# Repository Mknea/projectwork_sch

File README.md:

# Project work pcb design

This repository contains the KiCAD schematic and pcb layout files used in Project work course. The designed boards were used in conjunction with developed mobile app to automate a popular finnish outdoor game, Mölkky.

Both macro- and microboard-versions of the design were manufactured, components were soldered in, and the proper functioning of the whole product was both verified and demonstrated.

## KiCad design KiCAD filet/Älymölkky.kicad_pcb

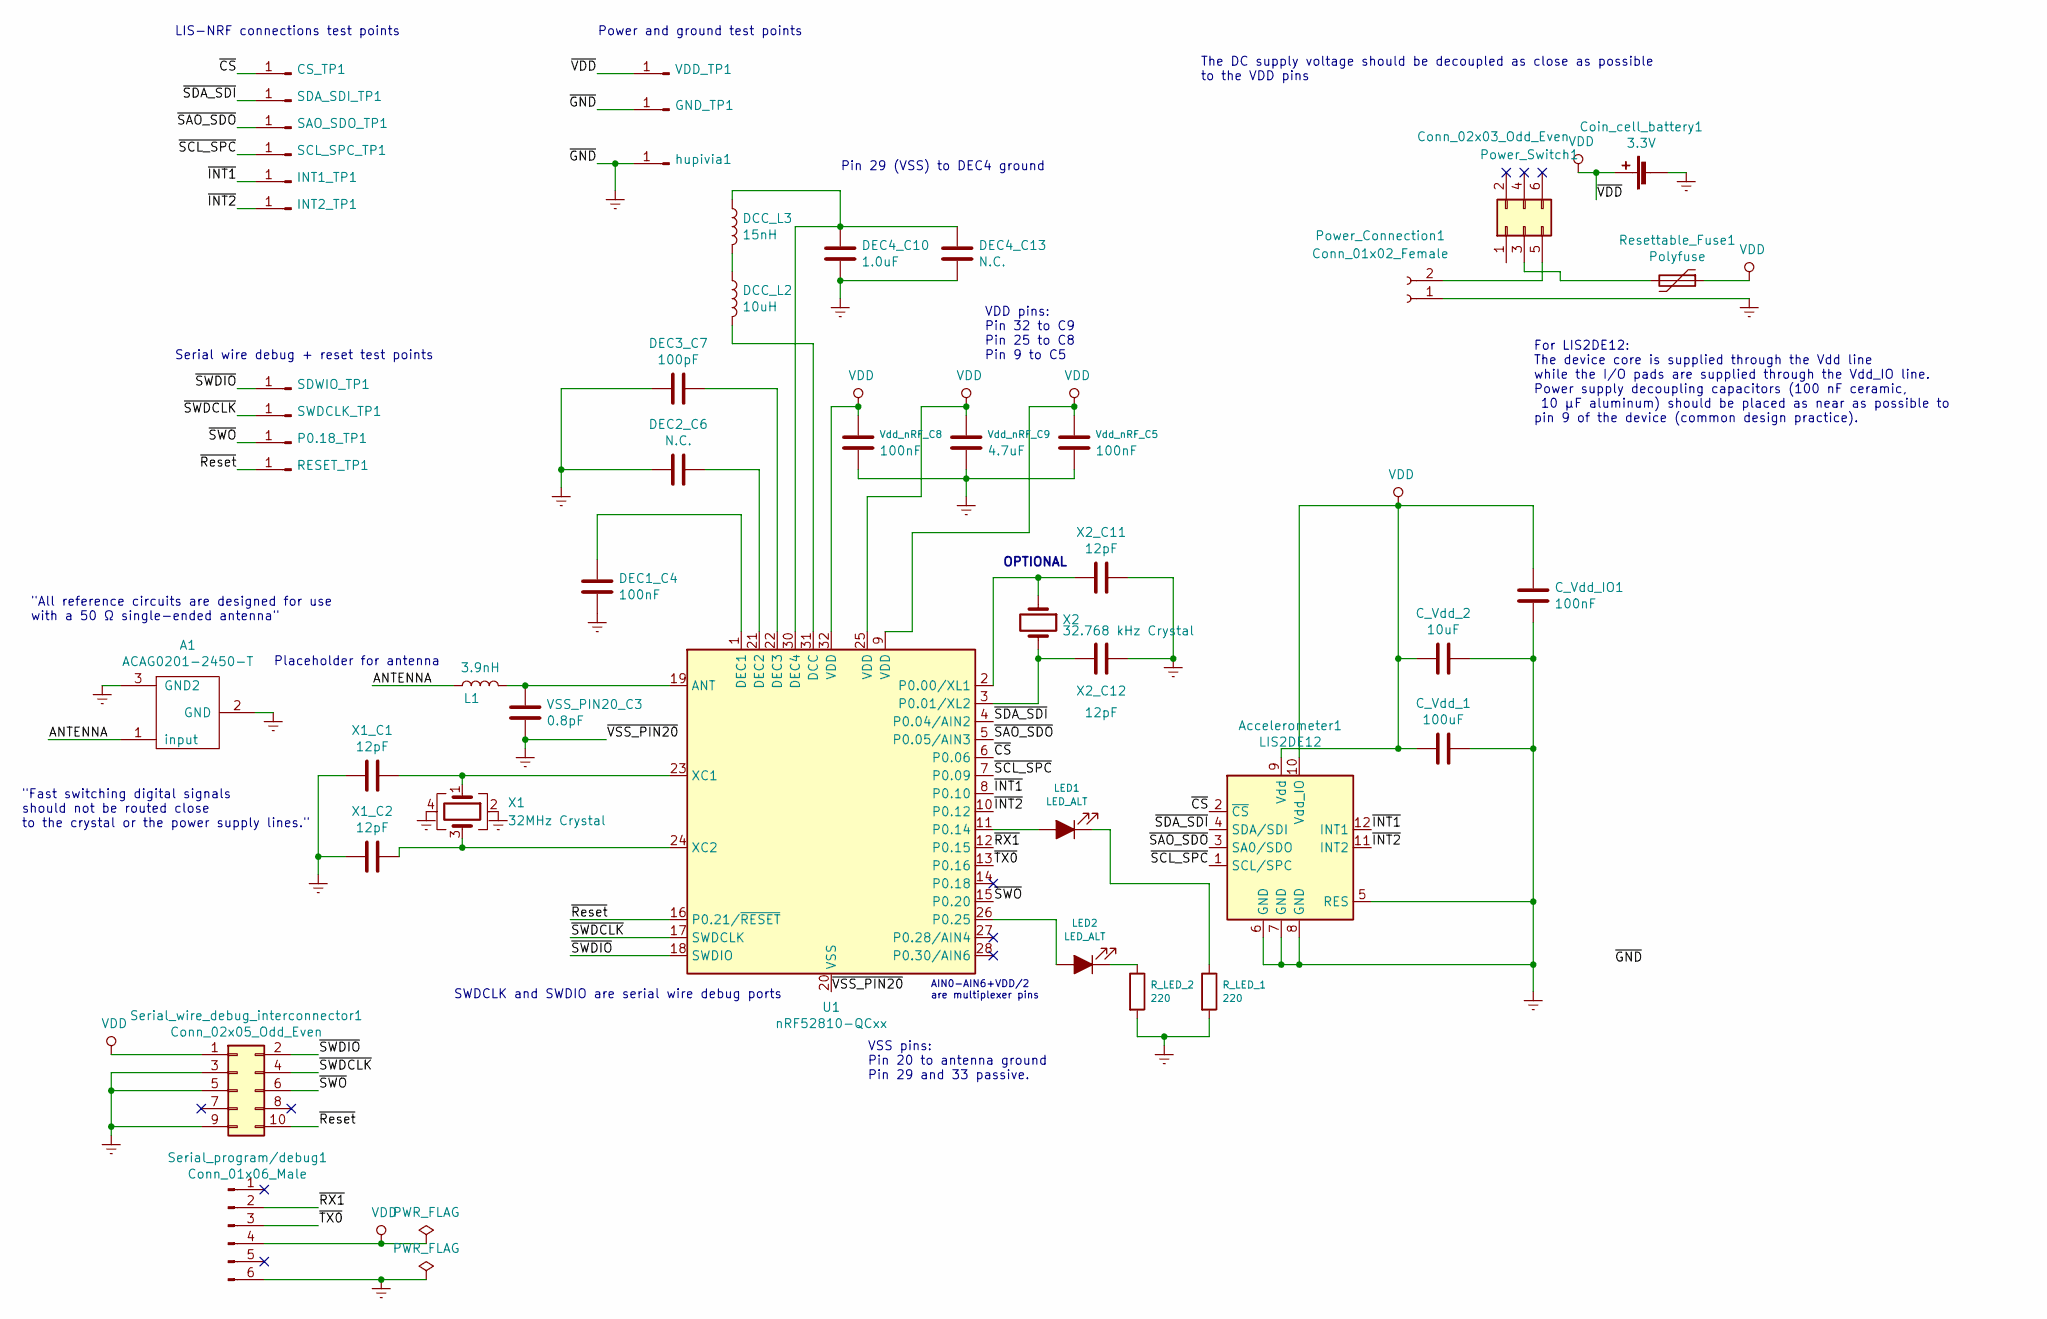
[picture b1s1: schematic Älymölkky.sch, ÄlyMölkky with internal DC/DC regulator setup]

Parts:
A1: ACAG0201-2450-T
Accelerometer1: LIS2DE12; LGA-12_2x2mm_P0.5mm
CS_TP1: Conn_01x01_Male; PinHeader_1x01_P2.54mm_Vertical
C_Vdd_1: 100uF; C_0805_2012Metric_Pad1.15x1.40mm_HandSolder
C_Vdd_2: 10uF; C_0805_2012Metric_Pad1.15x1.40mm_HandSolder
C_Vdd_IO1: 100nF; C_0805_2012Metric_Pad1.15x1.40mm_HandSolder
Coin_cell_battery1: 3.3V
DCC_L2: 10uH; C_0805_2012Metric_Pad1.15x1.40mm_HandSolder
DCC_L3: 15nH; C_0402_1005Metric
DEC1_C4: 100nF; C_0805_2012Metric_Pad1.15x1.40mm_HandSolder
DEC2_C6, DEC4_C13: N.C.; C_0805_2012Metric_Pad1.15x1.40mm_HandSolder
DEC3_C7: 100pF; C_0805_2012Metric_Pad1.15x1.40mm_HandSolder
DEC4_C10: 1.0uF; C_0805_2012Metric_Pad1.15x1.40mm_HandSolder
GND_TP1: Conn_01x01_Male; PinHeader_1x01_P2.54mm_Vertical
INT1_TP1, INT2_TP1: Conn_01x01_Male; PinHeader_1x01_P2.54mm_Vertical
L1: 3.9nH; R_0402_1005Metric
LED1, LED2: LED_ALT; R_0805_2012Metric_Pad1.15x1.40mm_HandSolder
P0.18_TP1: Conn_01x01_Male; PinHeader_1x01_P2.54mm_Vertical
Power_Connection1: Conn_01x02_Female; PinHeader_1x02_P2.54mm_Vertical
Power_Switch1: Conn_02x03_Odd_Even; PinHeader_2x03_P1.27mm_Vertical_SMD
RESET_TP1: Conn_01x01_Male; PinHeader_1x01_P2.54mm_Vertical
R_LED_1, R_LED_2: 220; R_0805_2012Metric_Pad1.15x1.40mm_HandSolder
Resettable_Fuse1: Polyfuse; R_0805_2012Metric_Pad1.15x1.40mm_HandSolder
SAO_SDO_TP1: Conn_01x01_Male; PinHeader_1x01_P2.54mm_Vertical
SCL_SPC_TP1: Conn_01x01_Male; PinHeader_1x01_P2.54mm_Vertical
SDA_SDI_TP1: Conn_01x01_Male; PinHeader_1x01_P2.54mm_Vertical
SDWIO_TP1: Conn_01x01_Male; PinHeader_1x01_P2.54mm_Vertical
SWDCLK_TP1: Conn_01x01_Male; PinHeader_1x01_P2.54mm_Vertical
Serial_program/debug1: Conn_01x06_Male; PinHeader_1x06_P2.54mm_Vertical
Serial_wire_debug_interconnector1: Conn_02x05_Odd_Even; PinHeader_2x05_P1.27mm_Vertical_SMD
U1: nRF52810-QCxx; QFN-32-1EP_5x5mm_P0.5mm_EP3.6x3.6mm
VDD_TP1: Conn_01x01_Male; PinHeader_1x01_P2.54mm_Vertical
VSS_PIN20_C3: 0.8pF; C_0402_1005Metric
Vdd_nRF_C5, Vdd_nRF_C8: 100nF; C_0805_2012Metric_Pad1.15x1.40mm_HandSolder
Vdd_nRF_C9: 4.7uF; C_0805_2012Metric_Pad1.15x1.40mm_HandSolder
X1: 32MHz Crystal; Crystal_3.2x2.5x0.8
X1_C1, X1_C2, X2_C11, X2_C12: 12pF; C_0805_2012Metric_Pad1.15x1.40mm_HandSolder
X2: 32.768 kHz Crystal; Crystal_SMD_3215-2Pin_3.2x1.5mm
hupivia1: Conn_01x01_Male; PinHeader_1x01_P2.54mm_Vertical

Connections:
/ANTENNA: A1.1 (input), L1.1
/~CS: Accelerometer1.2 (~CS), CS_TP1.1, U1.6 (P0.06)
/~INT1: Accelerometer1.12 (INT1), INT1_TP1.1, U1.8 (P0.10)
/~INT2: Accelerometer1.11 (INT2), INT2_TP1.1, U1.10 (P0.12)
/~RX1: Serial_program/debug1.2, U1.12 (P0.15)
/~Reset: RESET_TP1.1, Serial_wire_debug_interconnector1.10, U1.16 (P0.21/~RESET)
/~SAO_SDO: Accelerometer1.3 (SA0/SDO), SAO_SDO_TP1.1, U1.5 (P0.05/AIN3)
/~SCL_SPC: Accelerometer1.1 (SCL/SPC), SCL_SPC_TP1.1, U1.7 (P0.09)
/~SDA_SDI: Accelerometer1.4 (SDA/SDI), SDA_SDI_TP1.1, U1.4 (P0.04/AIN2)
/~SWDCLK: SWDCLK_TP1.1, Serial_wire_debug_interconnector1.4, U1.17 (SWDCLK)
/~SWDIO: SDWIO_TP1.1, Serial_wire_debug_interconnector1.2, U1.18 (SWDIO)
/~SWO: P0.18_TP1.1, Serial_wire_debug_interconnector1.6, U1.15 (P0.20)
/~TX0: Serial_program/debug1.3, U1.13 (P0.16)
Earth: A1.2 (GND), A1.3 (GND2), Accelerometer1.5 (RES), Accelerometer1.6 (GND), Accelerometer1.7 (GND), Accelerometer1.8 (GND), C_Vdd_1.2, C_Vdd_2.2, C_Vdd_IO1.2, Coin_cell_battery1.2 (-), DEC1_C4.2, DEC2_C6.2, DEC3_C7.2, DEC4_C10.2, DEC4_C13.2, GND_TP1.1, Power_Connection1.1, R_LED_1.2, R_LED_2.2, Serial_program/debug1.6, Serial_wire_debug_interconnector1.3, Serial_wire_debug_interconnector1.5, Serial_wire_debug_interconnector1.9, U1.20 (VSS), U1.29 (VSS), U1.33 (VSS), VSS_PIN20_C3.2, Vdd_nRF_C5.2, Vdd_nRF_C8.2, Vdd_nRF_C9.2, X1.2, X1.4, X1_C1.2, X1_C2.2, X2_C11.1, X2_C12.1, hupivia1.1
unnamed: DCC_L2.1, DCC_L3.2
unnamed: DCC_L2.2, U1.31 (DCC)
unnamed: DCC_L3.1, DEC4_C10.1, DEC4_C13.1, U1.30 (DEC4)
unnamed: DEC1_C4.1, U1.1 (DEC1)
unnamed: DEC2_C6.1, U1.21 (DEC2)
unnamed: DEC3_C7.1, U1.22 (DEC3)
unnamed: L1.2, U1.19 (ANT), VSS_PIN20_C3.1
unnamed: LED1.1 (K), R_LED_1.1
unnamed: LED1.2 (A), U1.11 (P0.14)
unnamed: LED2.1 (K), R_LED_2.1
unnamed: LED2.2 (A), U1.26 (P0.25)
unnamed: Power_Connection1.2, Power_Switch1.5
unnamed: Power_Switch1.3, Resettable_Fuse1.2
unnamed: U1.2 (P0.00/XL1), X2.1, X2_C11.2
unnamed: U1.3 (P0.01/XL2), X2.2, X2_C12.2
unnamed: U1.23 (XC1), X1.1, X1_C1.1
unnamed: U1.24 (XC2), X1.3, X1_C2.1
VDD: Accelerometer1.9 (Vdd), Accelerometer1.10 (Vdd_IO), C_Vdd_1.1, C_Vdd_2.1, C_Vdd_IO1.1, Coin_cell_battery1.1 (+), Resettable_Fuse1.1, Serial_program/debug1.4, Serial_wire_debug_interconnector1.1, U1.9 (VDD), U1.25 (VDD), U1.32 (VDD), VDD_TP1.1, Vdd_nRF_C5.1, Vdd_nRF_C8.1, Vdd_nRF_C9.1

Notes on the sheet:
For LIS2DE12: The device core is supplied through the Vdd line while the I/O pads are supplied through the Vdd_IO line. Power supply decoupling capacitors (100 nF ceramic, 10 μF aluminum) should be placed as near as possible to pin 9 of the device (common design practice).
VDD pins: Pin 32 to C9 Pin 25 to C8 Pin 9 to C5
Pin 29 (VSS) to DEC4 ground
OPTIONAL
AIN0-AIN6+VDD/2 are multiplexer pins
SWDCLK and SWDIO are serial wire debug ports
Placeholder for antenna
VSS pins: Pin 20 to antenna ground Pin 29 and 33 passive.
LIS-NRF connections test points
Power and ground test points
Serial wire debug + reset test points
"All reference circuits are designed for use with a 50 Ω single-ended antenna"
The DC supply voltage should be decoupled as close as possible to the VDD pins
"Fast switching digital signals should not be routed close to the crystal or the power supply lines."

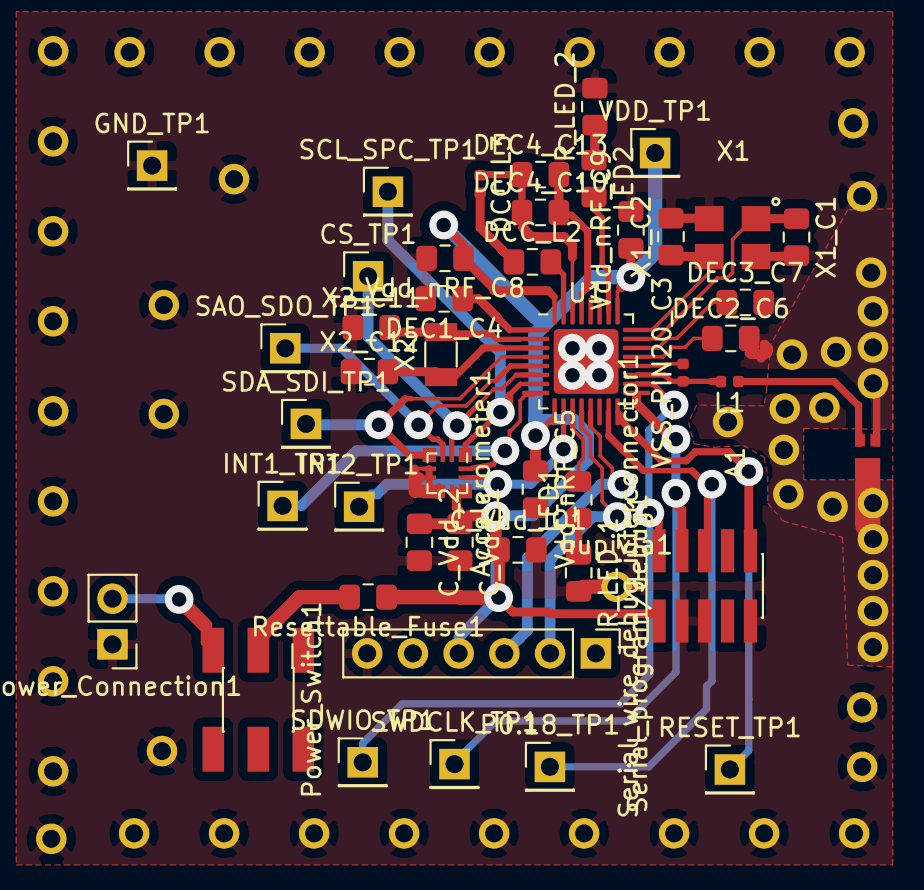
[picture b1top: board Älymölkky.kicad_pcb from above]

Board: 2 copper layers, 46 parts (0 on the bottom side), 32 nets.

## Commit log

2019-02-06 Added README.md file
2019-02-06 Datasheetit pääkomponenteista ja ref. schematic microcontrollerille
2019-02-06 Added file placeholder into new folder KiCAD filet
2019-02-06 Initial schematic
2019-02-07 Refactored folder structure
2019-02-07 Added lots of new reference files and a new lib
2019-02-07 Removed redundant files and more cleanup
2019-02-07 Added separate schematic for breakout board (done using nRF52832, not 10!)
2019-02-07 Breakout and dev schematics added.
2019-02-11 Added most of nrf52 pin connections
2019-02-11 Added comments on some pins
2019-02-12 Added newly named custom libraries
2019-02-12 Added test points, leds and serial port programming pins
2019-02-12 Added PCB component layouts
2019-02-14 Changed the circuit to allow internal DC/DC converter to be used
2019-02-14 Added pcb layouts for components and initialized the layout work
2019-02-18 Added fuse, modified nRF and LIS footprints and started layout work
2019-02-22 Added more traces, shifted one pin's place and will shift more soon
2019-02-22 Reorganized more pins, drew LIS traces
2019-02-25 Drew most of remaining traces, missing antenna and switch
2019-02-26 Added changes made by Pyry, antenna, copper pour and slight changes
2019-02-26 Added switch, modified components to right sizes
2019-02-26 Preparations for drilling
2019-03-01 Modified some traces, larger size capacitors on crystal
2019-03-12 Added microboard as separate folder with separate designs
2019-03-12 Changed programming interface to standalone pinheaders
2019-03-15 Re-arranged most of the layout to more compact form, missing antennas
2019-03-18 Changed serial programming pin locations and order, reorganized whole board
2019-03-22 Changed all vias to smaller size, passed electronic rule check
2019-03-26 Added battery vias and drew preliminary trace antenna
2019-03-26 Added new file for order with trace antenna, multiplied the ceramic antenna order pcb for order
2019-03-28 Staging to build traceantenna
2019-03-28 Readymade design with antenna, only antenna connection not wide enough, needs 3mm
2019-03-28 Trace antenna design completed, modifying for order
2019-03-28 Order ready trace antenna design
2020-05-20 Added folder for some pictures
2020-05-20 Added pictures of the development process
